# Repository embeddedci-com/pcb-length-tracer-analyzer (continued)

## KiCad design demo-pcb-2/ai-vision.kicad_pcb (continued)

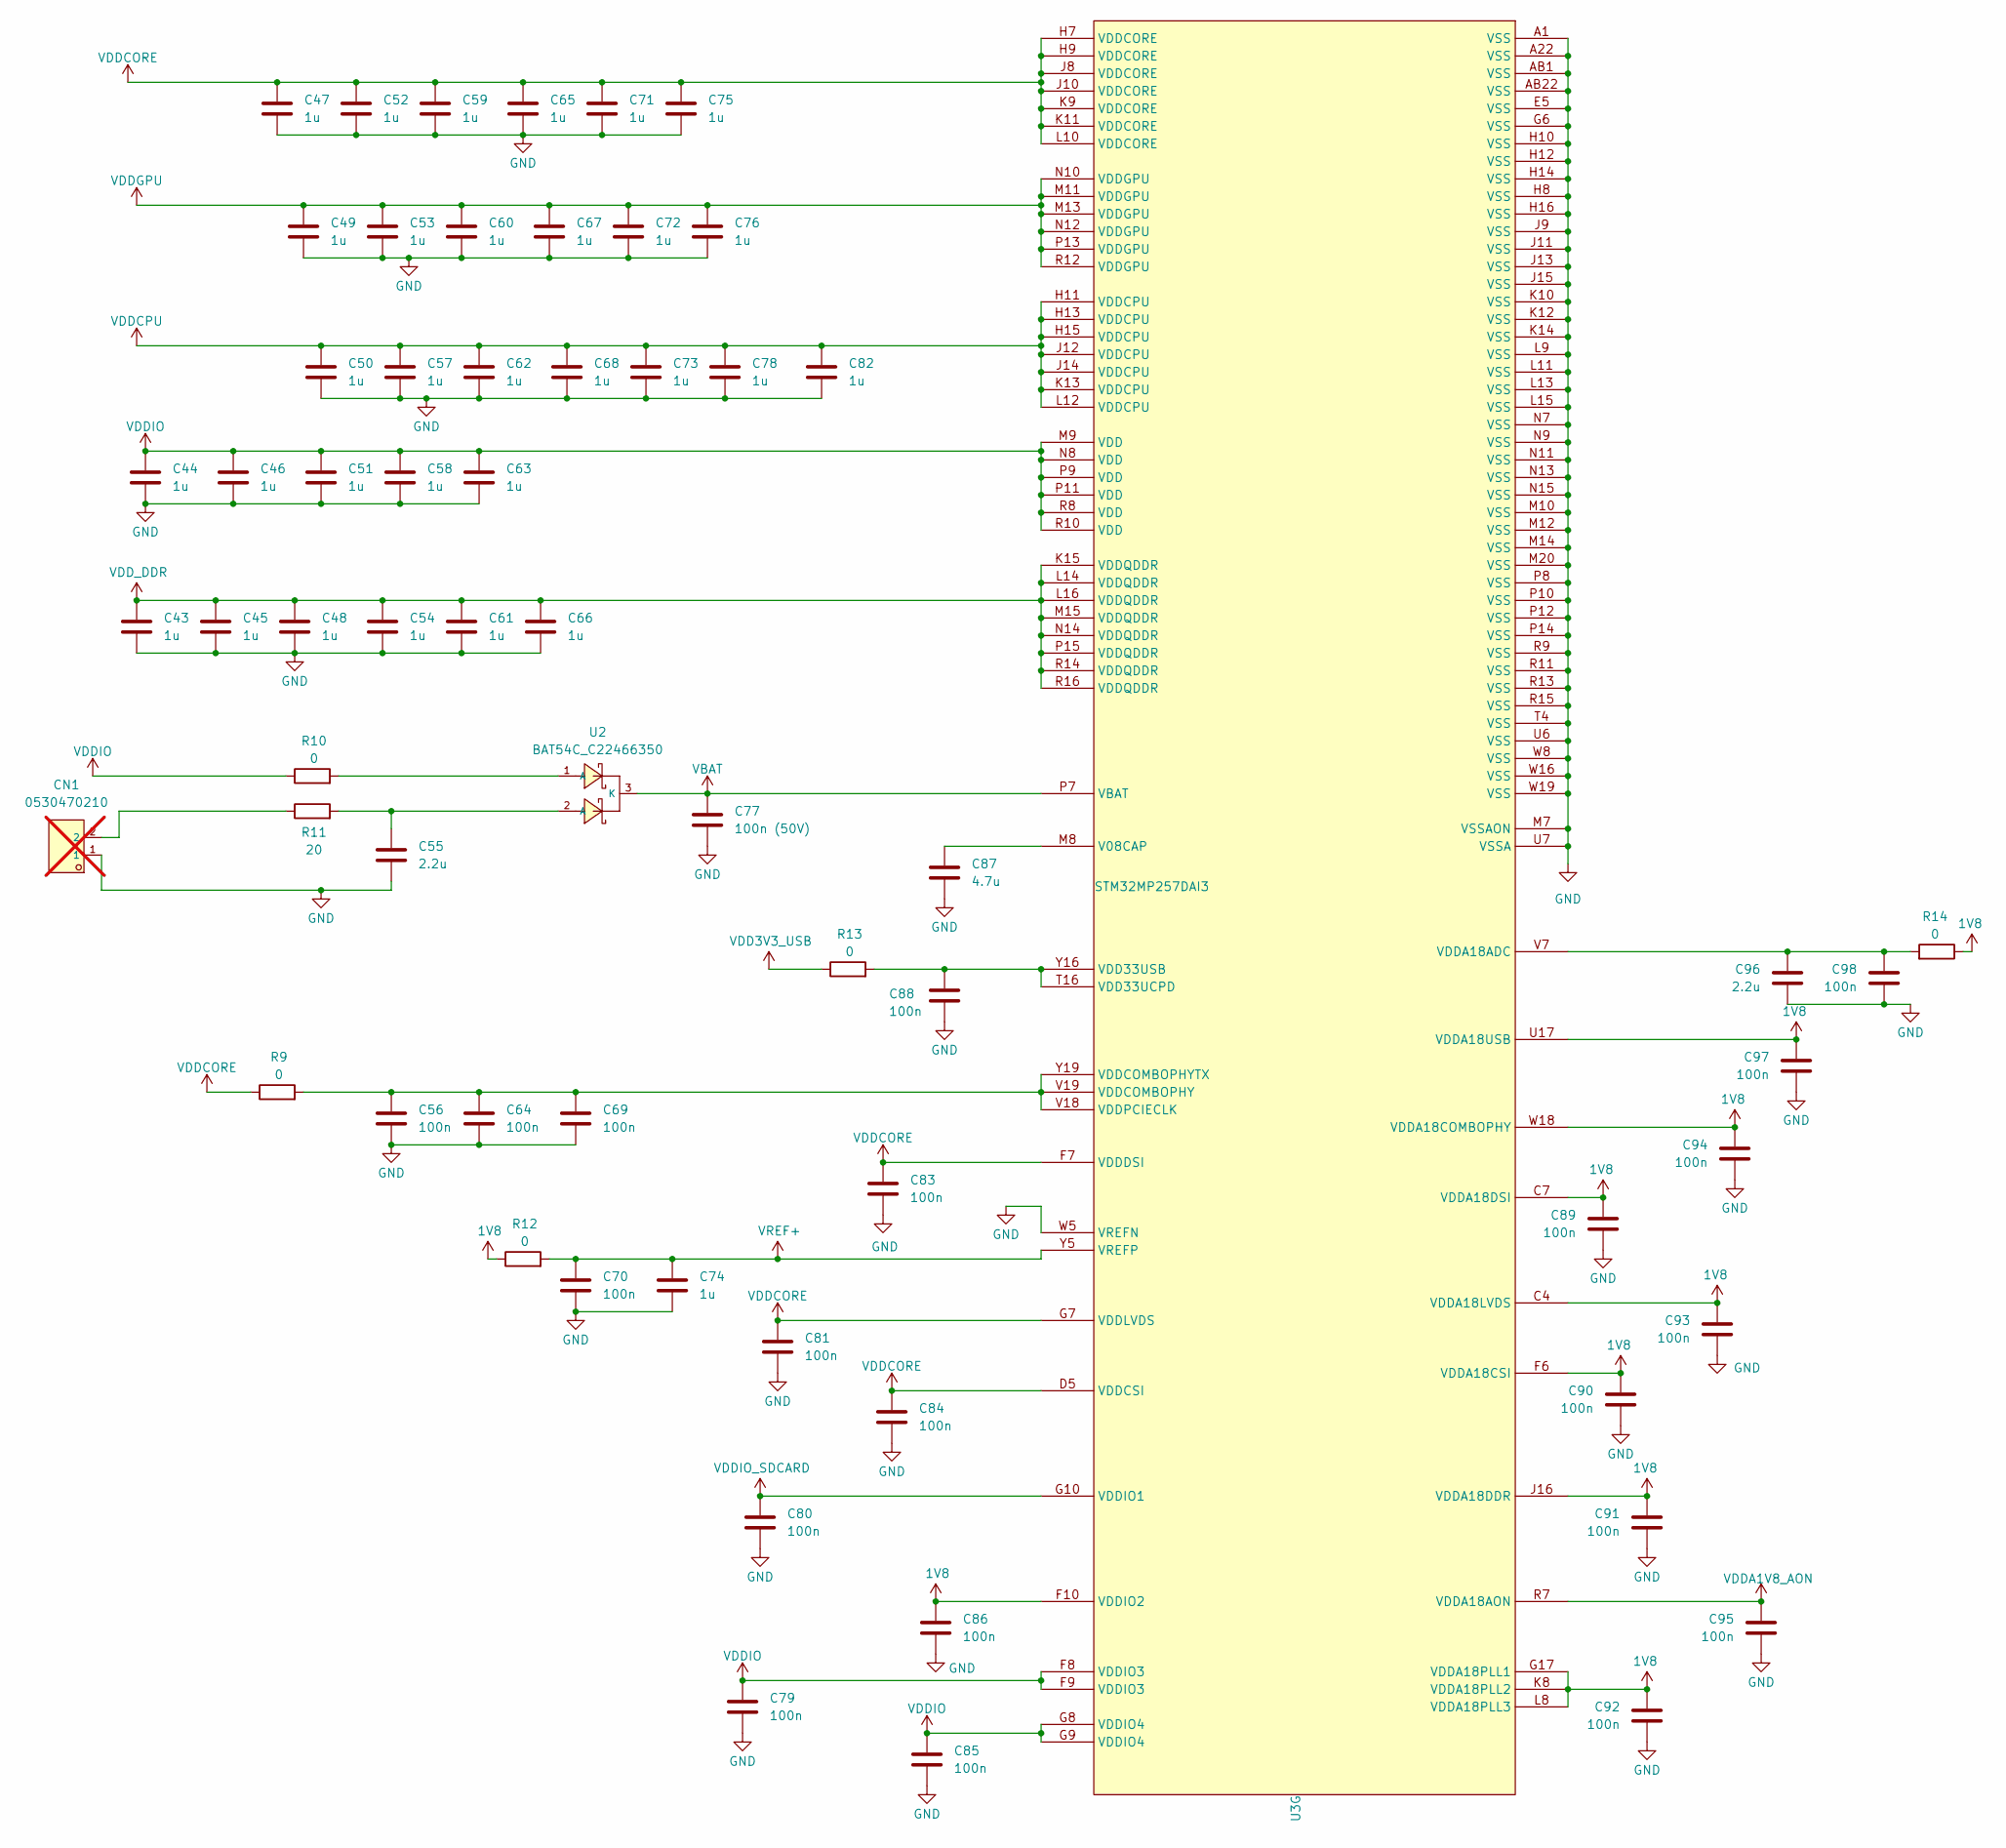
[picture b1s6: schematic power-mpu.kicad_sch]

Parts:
C43, C44, C45, C46, C47, C48, C49, C50, C51, C52, C53, C54, C57, C58, C59, C60, C61, C62, C63, C65, C66, C67, C68, C71, C72, C73, C74, C75, C76, C78, C82: 1u; C_0201_0603Metric; LCSC C76930
C55, C96: 2.2u; C_0805_2012Metric; LCSC C377773
C56, C64, C69, C70, C79, C80, C81, C83, C84, C85, C86, C88, C89, C90, C91, C92, C93, C94, C95, C97, C98: 100n; C_0201_0603Metric; LCSC C76934
C77: 100n (50V); C_0402_1005Metric; LCSC C307331
C87: 4.7u; C_0805_2012Metric; LCSC C1779
CN1: 0530470210; C114130_CONN-TH_0530470210; LCSC C114130; not fitted
R9, R10, R12, R13, R14: 0; R_0402_1005Metric; LCSC C17168
R11: 20; R_0603_1608Metric; LCSC C22950
U2: BAT54C_C22466350; C22466350_SOT-23-3_L2_9-W1_3-P1_90-LS2_8-BR; LCSC C22466350
U3: STM32MP257DAI3; C39969643_TFBGA-436_L18_0-W18_0-0_80-TL_STM32MP257FAI3; PART_TYPE IC; LCSC C39969643

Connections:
1V8: C86.1, C89.1, C90.1, C91.1, C92.1, C93.1, C94.1, C97.1, R12.1, R14.1, U3.C4 (VDDA18LVDS), U3.C7 (VDDA18DSI), U3.F6 (VDDA18CSI), U3.F10 (VDDIO2), U3.G17 (VDDA18PLL1), U3.J16 (VDDA18DDR), U3.K8 (VDDA18PLL2), U3.L8 (VDDA18PLL3), U3.U17 (VDDA18USB), U3.W18 (VDDA18COMBOPHY); also elsewhere on the board
GND: C43.2, C44.2, C45.2, C46.2, C47.2, C48.2, C49.2, C50.2, C51.2, C52.2, C53.2, C54.2, C55.2, C56.2, C57.2, C58.2, C59.2, C60.2, C61.2, C62.2, C63.2, C64.2, C65.2, C66.2, C67.2, C68.2, C69.2, C70.2, C71.2, C72.2, C73.2, C74.2, C75.2, C76.2, C77.2, C78.2, C79.2, C80.2, C81.2, C82.2, C83.2, C84.2, C85.2, C86.2, C87.2, C88.2, C89.2, C90.2, C91.2, C92.2, C93.2, C94.2, C95.2, C96.2, C97.2, C98.2, CN1.1, U3.A1 (VSS), U3.A22 (VSS), U3.AB1 (VSS), U3.AB22 (VSS), U3.E5 (VSS), U3.G6 (VSS), U3.H8 (VSS), U3.H10 (VSS), U3.H12 (VSS), U3.H14 (VSS), U3.H16 (VSS), U3.J9 (VSS), U3.J11 (VSS), U3.J13 (VSS), U3.J15 (VSS), U3.K10 (VSS), U3.K12 (VSS), U3.K14 (VSS), U3.L9 (VSS), U3.L11 (VSS), U3.L13 (VSS), U3.L15 (VSS), U3.M7 (VSSAON), U3.M10 (VSS), U3.M12 (VSS), U3.M14 (VSS), U3.M20 (VSS), U3.N7 (VSS), U3.N9 (VSS), U3.N11 (VSS), U3.N13 (VSS), U3.N15 (VSS), U3.P8 (VSS), U3.P10 (VSS), U3.P12 (VSS), U3.P14 (VSS), U3.R9 (VSS), U3.R11 (VSS), U3.R13 (VSS), U3.R15 (VSS), U3.T4 (VSS), U3.U6 (VSS), U3.U7 (VSSA), U3.W5 (VREFN), U3.W8 (VSS), U3.W16 (VSS), U3.W19 (VSS); also elsewhere on the board
unnamed: C55.1, R11.2, U2.2 (A)
unnamed: CN1.2, R11.1
unnamed: R10.2, U2.1 (A)
unnamed: C87.1, U3.M8 (V08CAP)
unnamed: C88.1, R13.2, U3.T16 (VDD33UCPD), U3.Y16 (VDD33USB)
unnamed: C96.1, C98.1, R14.2, U3.V7 (VDDA18ADC)
unnamed: C56.1, C64.1, C69.1, R9.2, U3.V18 (VDDPCIECLK), U3.V19 (VDDCOMBOPHY), U3.Y19 (VDDCOMBOPHYTX)
VBAT: C77.1, U2.3 (K), U3.P7 (VBAT)
VDD3V3_USB: R13.1; also elsewhere on the board
VDDA1V8_AON: C95.1, U3.R7 (VDDA18AON); also elsewhere on the board
VDDCORE: C47.1, C52.1, C59.1, C65.1, C71.1, C75.1, C81.1, C83.1, C84.1, R9.1, U3.D5 (VDDCSI), U3.F7 (VDDDSI), U3.G7 (VDDLVDS), U3.H7 (VDDCORE), U3.H9 (VDDCORE), U3.J8 (VDDCORE), U3.J10 (VDDCORE), U3.K9 (VDDCORE), U3.K11 (VDDCORE), U3.L10 (VDDCORE); also elsewhere on the board
VDDCPU: C50.1, C57.1, C62.1, C68.1, C73.1, C78.1, C82.1, U3.H11 (VDDCPU), U3.H13 (VDDCPU), U3.H15 (VDDCPU), U3.J12 (VDDCPU), U3.J14 (VDDCPU), U3.K13 (VDDCPU), U3.L12 (VDDCPU); also elsewhere on the board
VDDGPU: C49.1, C53.1, C60.1, C67.1, C72.1, C76.1, U3.M11 (VDDGPU), U3.M13 (VDDGPU), U3.N10 (VDDGPU), U3.N12 (VDDGPU), U3.P13 (VDDGPU), U3.R12 (VDDGPU)
VDDIO: C44.1, C46.1, C51.1, C58.1, C63.1, C79.1, C85.1, R10.1, U3.F8 (VDDIO3), U3.F9 (VDDIO3), U3.G8 (VDDIO4), U3.G9 (VDDIO4), U3.M9 (VDD), U3.N8 (VDD), U3.P9 (VDD), U3.P11 (VDD), U3.R8 (VDD), U3.R10 (VDD); also elsewhere on the board
VDDIO_SDCARD: C80.1, U3.G10 (VDDIO1); also elsewhere on the board
VDD_DDR: C43.1, C45.1, C48.1, C54.1, C61.1, C66.1, U3.K15 (VDDQDDR), U3.L14 (VDDQDDR), U3.L16 (VDDQDDR), U3.M15 (VDDQDDR), U3.N14 (VDDQDDR), U3.P15 (VDDQDDR), U3.R14 (VDDQDDR), U3.R16 (VDDQDDR); also elsewhere on the board
VREF+: C70.1, C74.1, R12.2, U3.Y5 (VREFP)

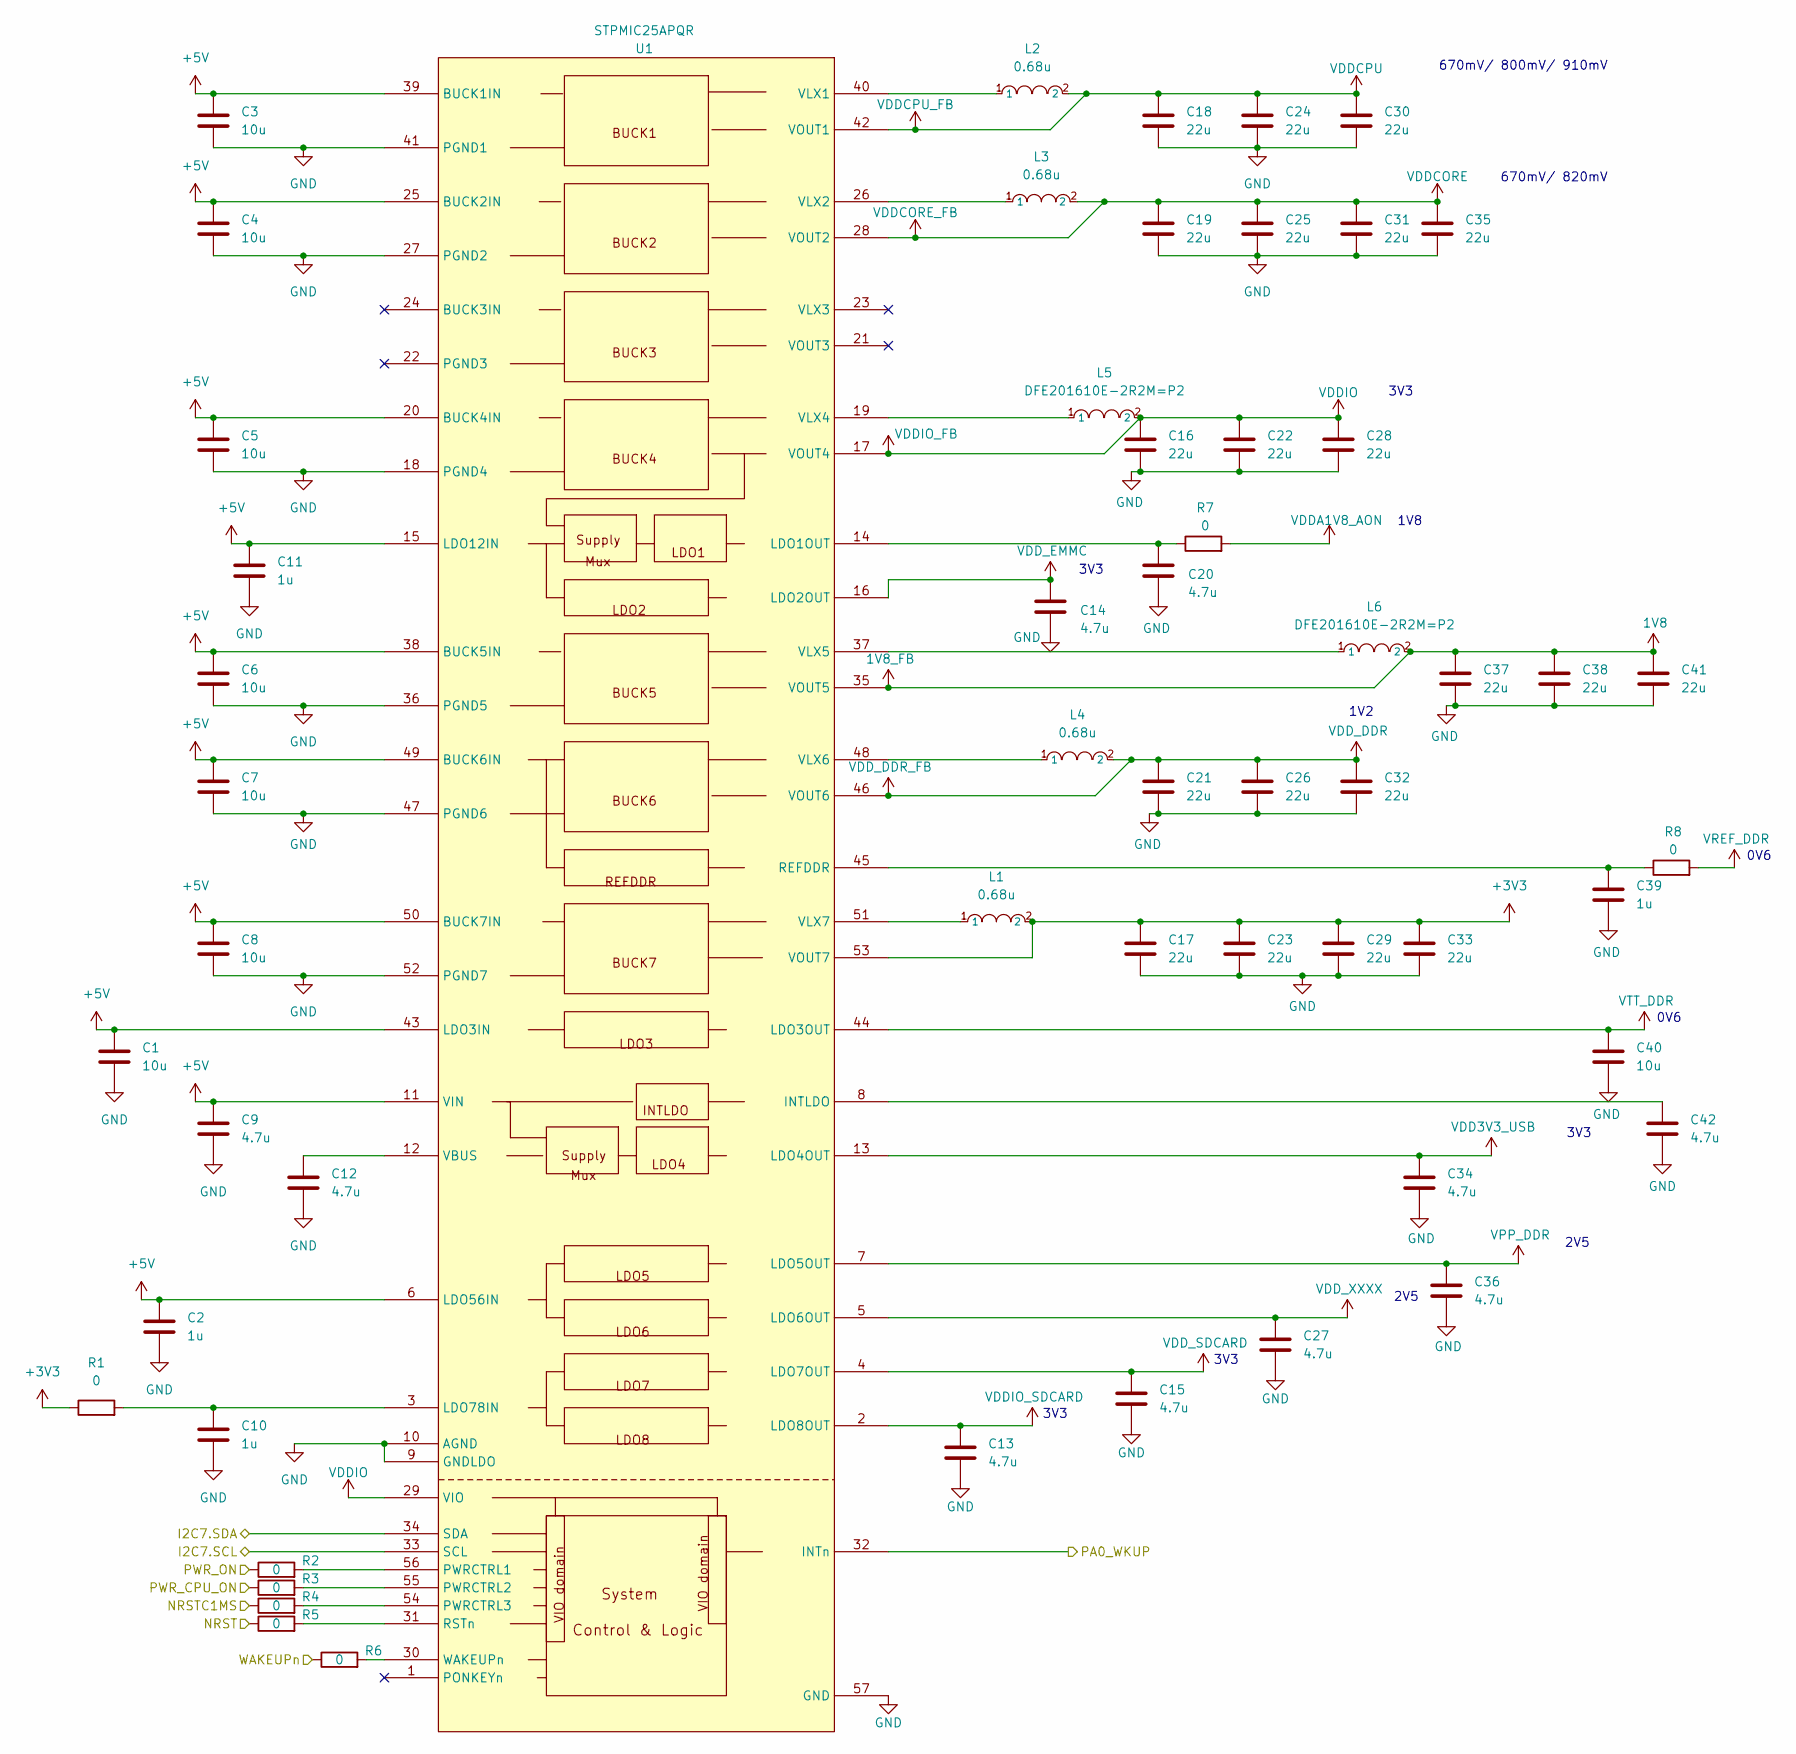
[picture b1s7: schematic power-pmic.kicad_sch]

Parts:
C1, C3, C4, C5, C6, C7, C8, C40: 10u; C_0603_1608Metric; LCSC C96446
C2, C10, C11, C39: 1u; C_0402_1005Metric; LCSC C52923
C9, C12, C13, C14, C15, C20, C27, C34, C36, C42: 4.7u; C_0805_2012Metric; LCSC C1779
C16, C17, C18, C19, C21, C22, C23, C24, C25, C26, C28, C29, C30, C31, C32, C33, C35, C37, C38, C41: 22u; C_0805_2012Metric; LCSC C45783
L1, L3: 0.68u; C2042379_L1008; LCSC C2042379
L2, L4: 0.68u; C237553_L0806; LCSC C237553
L5, L6: DFE201610E-2R2M=P2; C337891_L0806; LCSC C337891
R1, R2, R3, R4, R5, R6, R7, R8: 0; R_0402_1005Metric; LCSC C17168
U1: STPMIC2; C24290186_QFN-56_L6_5-W6_5-P0_40-TL-EP4_5; PART_TYPE IC; LCSC C24290186

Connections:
1V8: C37.1, C38.1, C41.1, L6.2, U1.35 (VOUT5); also elsewhere on the board
+3V3: C17.1, C23.1, C29.1, C33.1, L1.2, R1.1, U1.53 (VOUT7); also elsewhere on the board
+5V: C1.1, C2.1, C3.1, C4.1, C5.1, C6.1, C7.1, C8.1, C9.1, C11.1, U1.6 (LDO56IN), U1.11 (VIN), U1.15 (LDO12IN), U1.20 (BUCK4IN), U1.25 (BUCK2IN), U1.38 (BUCK5IN), U1.39 (BUCK1IN), U1.43 (LDO3IN), U1.49 (BUCK6IN), U1.50 (BUCK7IN); also elsewhere on the board
/MP257/I2C7.SCL: U1.33 (SCL); also elsewhere on the board
/MP257/I2C7.SDA: U1.34 (SDA); also elsewhere on the board
/MP257/PA0_WKUP: U1.32 (INTn); also elsewhere on the board
/MP257/PWR_CPU_ON: R3.1; also elsewhere on the board
/MP257/PWR_ON: R2.1; also elsewhere on the board
/MP257/WAKEUPn: R6.1; also elsewhere on the board
/NRST: R5.1; also elsewhere on the board
/NRSTC1MS: R4.1; also elsewhere on the board
GND: C1.2, C2.2, C3.2, C4.2, C5.2, C6.2, C7.2, C8.2, C9.2, C10.2, C11.2, C12.2, C13.2, C14.2, C15.2, C16.2, C17.2, C18.2, C19.2, C20.2, C21.2, C22.2, C23.2, C24.2, C25.2, C26.2, C27.2, C28.2, C29.2, C30.2, C31.2, C32.2, C33.2, C34.2, C35.2, C36.2, C37.2, C38.2, C39.2, C40.2, C41.2, C42.2, U1.9 (GNDLDO), U1.10 (AGND), U1.18 (PGND4), U1.27 (PGND2), U1.36 (PGND5), U1.41 (PGND1), U1.47 (PGND6), U1.52 (PGND7), U1.57 (GND); also elsewhere on the board
unnamed: C42.1, U1.8 (INTLDO)
unnamed: C20.1, R7.1, U1.14 (LDO1OUT)
unnamed: C10.1, R1.2, U1.3 (LDO78IN)
unnamed: R2.2, U1.56 (PWRCTRL1)
unnamed: R3.2, U1.55 (PWRCTRL2)
unnamed: R4.2, U1.54 (PWRCTRL3)
unnamed: C39.1, R8.1, U1.45 (REFDDR)
unnamed: R5.2, U1.31 (RSTn)
unnamed: C12.1, U1.12 (VBUS)
unnamed: L2.1, U1.40 (VLX1)
unnamed: L3.1, U1.26 (VLX2)
unnamed: L5.1, U1.19 (VLX4)
unnamed: L6.1, U1.37 (VLX5)
unnamed: L4.1, U1.48 (VLX6)
unnamed: L1.1, U1.51 (VLX7)
unnamed: R6.2, U1.30 (WAKEUPn)
VDD3V3_USB: C34.1, U1.13 (LDO4OUT); also elsewhere on the board
VDDA1V8_AON: R7.2; also elsewhere on the board
VDDCORE: C19.1, C25.1, C31.1, C35.1, L3.2, U1.28 (VOUT2); also elsewhere on the board
VDDCPU: C18.1, C24.1, C30.1, L2.2, U1.42 (VOUT1); also elsewhere on the board
VDDIO: C16.1, C22.1, C28.1, L5.2, U1.17 (VOUT4), U1.29 (VIO); also elsewhere on the board
VDDIO_SDCARD: C13.1, U1.2 (LDO8OUT); also elsewhere on the board
VDD_DDR: C21.1, C26.1, C32.1, L4.2, U1.46 (VOUT6); also elsewhere on the board
VDD_EMMC: C14.1, U1.16 (LDO2OUT); also elsewhere on the board
VDD_SDCARD: C15.1, U1.4 (LDO7OUT); also elsewhere on the board
VDD_XXXX: C27.1, U1.5 (LDO6OUT)
VPP_DDR: C36.1, U1.7 (LDO5OUT); also elsewhere on the board
VREF_DDR: R8.2; also elsewhere on the board
VTT_DDR: C40.1, U1.44 (LDO3OUT); also elsewhere on the board

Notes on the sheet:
1V8
3V3
1V2
670mV/ 800mV/ 910mV
2V5
670mV/ 820mV
0V6

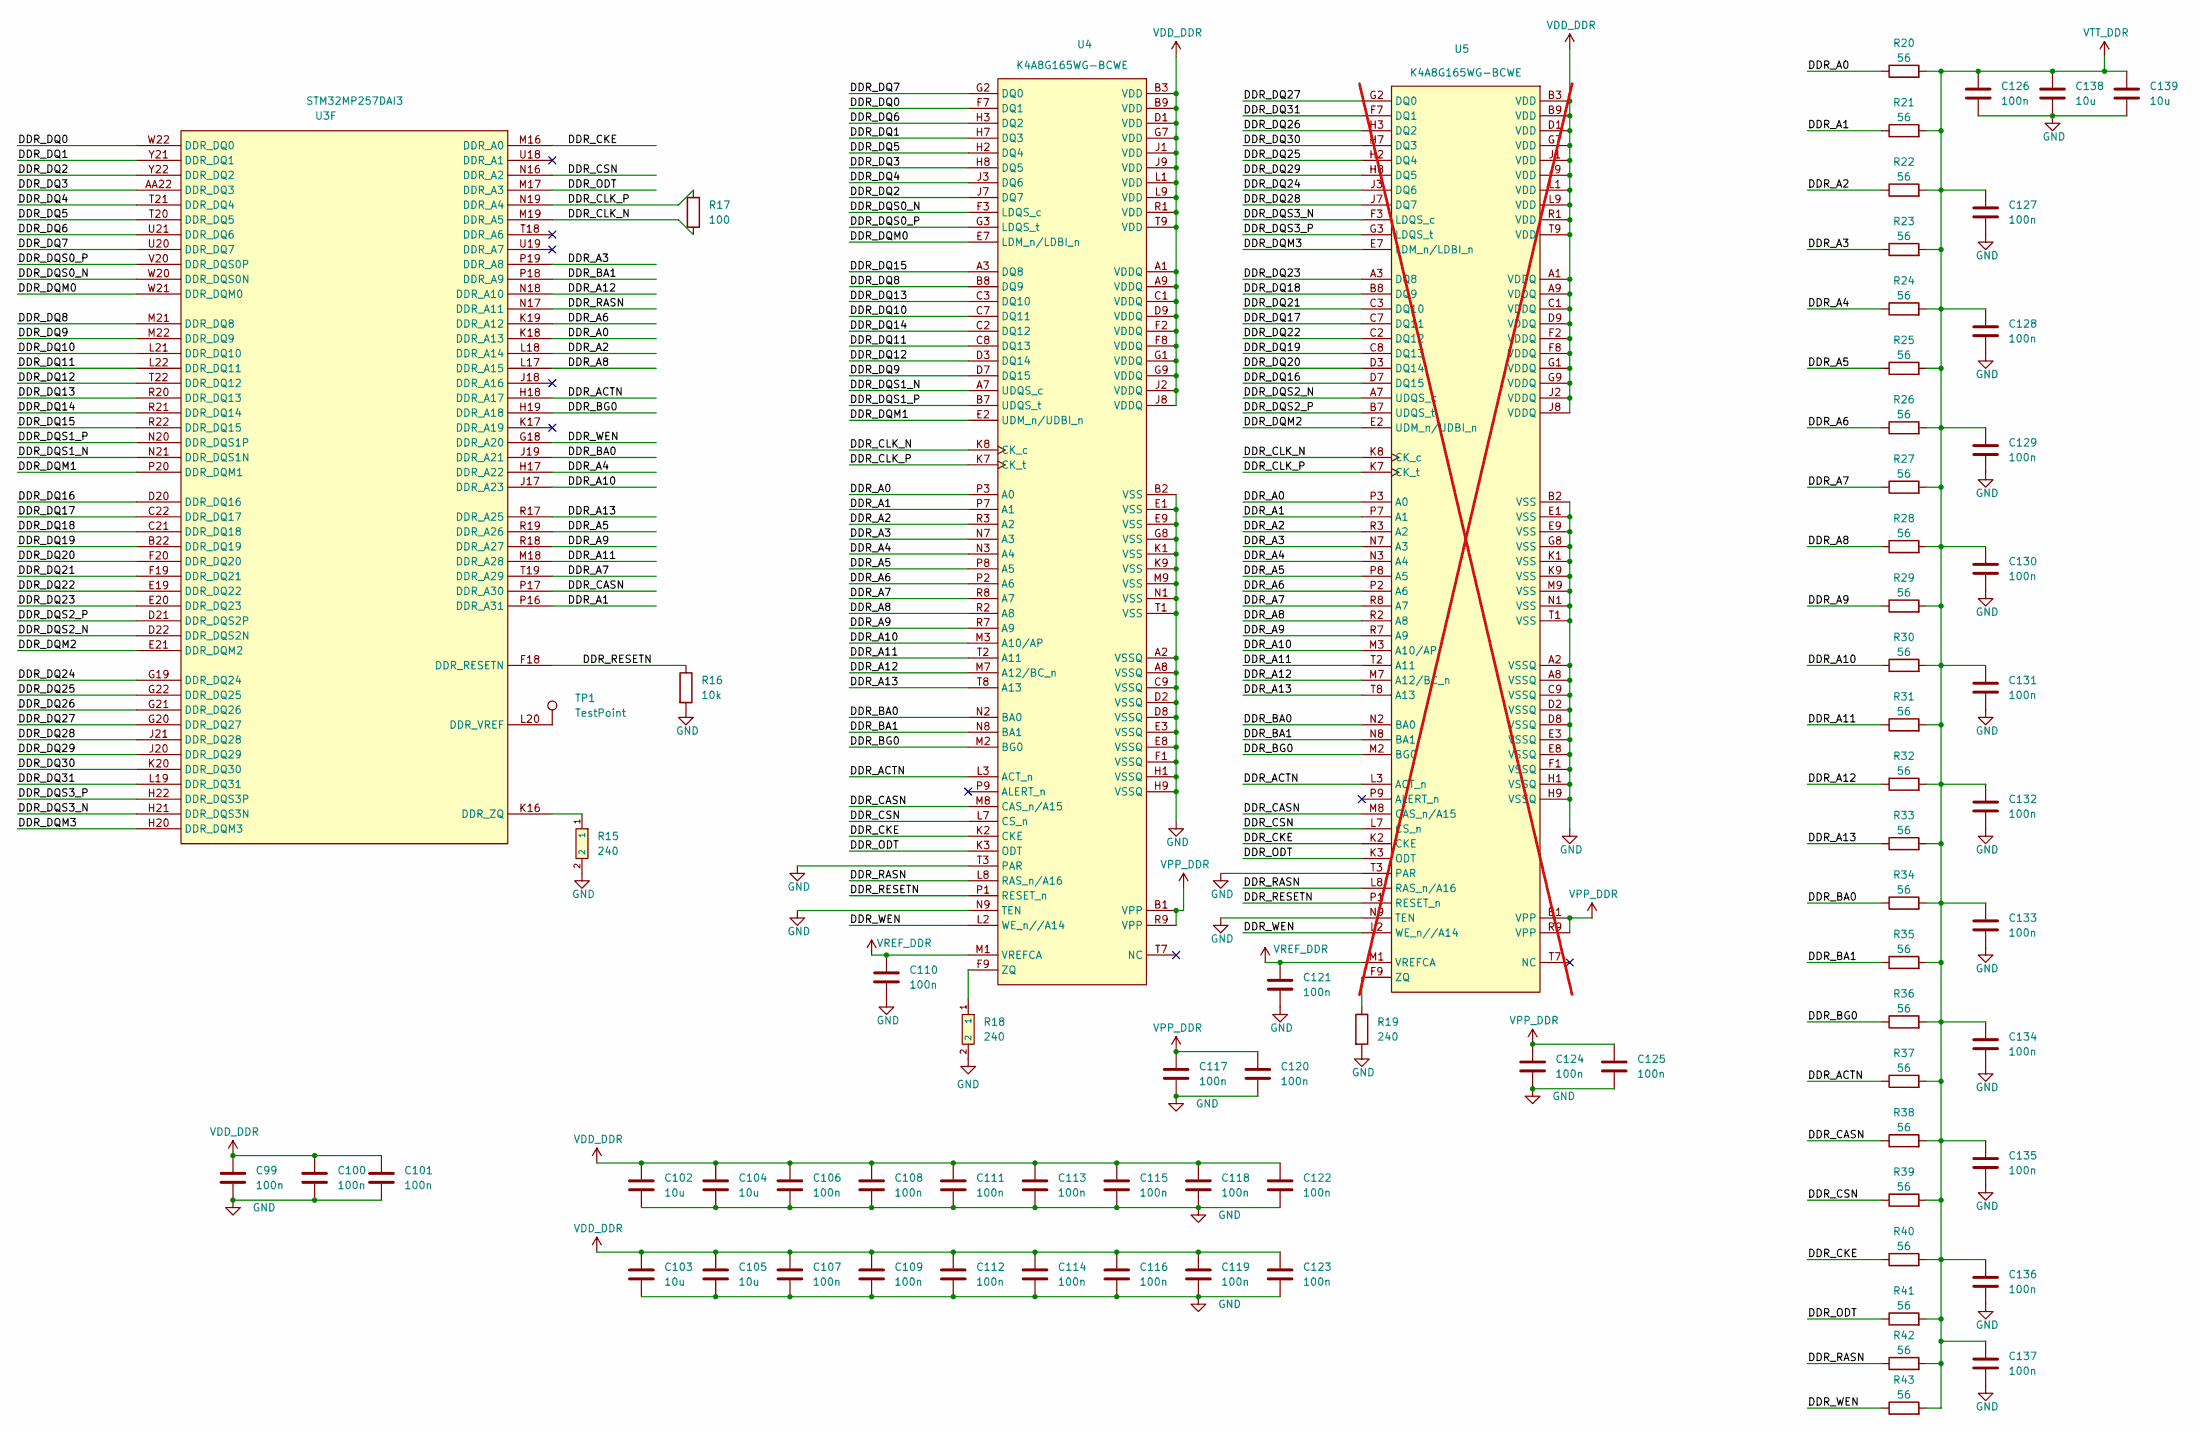
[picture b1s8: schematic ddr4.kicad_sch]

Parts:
C99, C100, C101, C106, C107, C108, C109, C110, C111, C112, C113, C114, C115, C116, C117, C118, C119, C120, C121, C122, C123, C124, C125, C126, C127, C128, C129, C130, C131, C132, C133, C134, C135, C136, C137: 100n; C_0402_1005Metric; LCSC C307331
C102, C103, C104, C105, C138, C139: 10u; C_0603_1608Metric; LCSC C96446
R15, R18: 240; C155745_R0201; LCSC C155745
R16: 10k; R_0402_1005Metric; LCSC C25744
R17: 100; R_0402_1005Metric; LCSC C25076
R19: 240; R_0603_1608Metric; LCSC C23350
R20, R21, R22, R23, R24, R25, R26, R27, R28, R29, R30, R31, R32, R33, R34, R35, R36, R37, R38, R39, R40, R41, R42, R43: 56; R_0402_1005Metric; LCSC C25127
TP1: TestPoint; TestPoint_Pad_1.0x1.0mm
U3: STM32MP257DAI3; C39969643_TFBGA-436_L18_0-W18_0-0_80-TL_STM32MP257FAI3; PART_TYPE IC; LCSC C39969643
U4: K4A8G165WG-BCWE; C41368581_FBGA-96_L13_3-W7_5-R16-C6-P0_80-TL; LCSC C41368581
U5: K4A8G165WG-BCWE; C41368581_FBGA-96_L13_3-W7_5-R16-C6-P0_80-TL; LCSC C41368581; not fitted

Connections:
/ddr4/DDR_A0: R20.1, U3.K18 (DDR_A13), U4.P3 (A0), U5.P3 (A0)
/ddr4/DDR_A1: R21.1, U3.P16 (DDR_A31), U4.P7 (A1), U5.P7 (A1)
/ddr4/DDR_A2: R22.1, U3.L18 (DDR_A14), U4.R3 (A2), U5.R3 (A2)
/ddr4/DDR_A3: R23.1, U3.P19 (DDR_A8), U4.N7 (A3), U5.N7 (A3)
/ddr4/DDR_A4: R24.1, U3.H17 (DDR_A22), U4.N3 (A4), U5.N3 (A4)
/ddr4/DDR_A5: R25.1, U3.R19 (DDR_A26), U4.P8 (A5), U5.P8 (A5)
/ddr4/DDR_A6: R26.1, U3.K19 (DDR_A12), U4.P2 (A6), U5.P2 (A6)
/ddr4/DDR_A7: R27.1, U3.T19 (DDR_A29), U4.R8 (A7), U5.R8 (A7)
/ddr4/DDR_A8: R28.1, U3.L17 (DDR_A15), U4.R2 (A8), U5.R2 (A8)
/ddr4/DDR_A9: R29.1, U3.R18 (DDR_A27), U4.R7 (A9), U5.R7 (A9)
/ddr4/DDR_A10: R30.1, U3.J17 (DDR_A23), U4.M3 (A10/AP), U5.M3 (A10/AP)
/ddr4/DDR_A11: R31.1, U3.M18 (DDR_A28), U4.T2 (A11), U5.T2 (A11)
/ddr4/DDR_A12: R32.1, U3.N18 (DDR_A10), U4.M7 (A12/BC_n), U5.M7 (A12/BC_n)
/ddr4/DDR_A13: R33.1, U3.R17 (DDR_A25), U4.T8 (A13), U5.T8 (A13)
/ddr4/DDR_ACTN: R37.1, U3.H18 (DDR_A17), U4.L3 (ACT_n), U5.L3 (ACT_n)
/ddr4/DDR_BA0: R34.1, U3.J19 (DDR_A21), U4.N2 (BA0), U5.N2 (BA0)
/ddr4/DDR_BA1: R35.1, U3.P18 (DDR_A9), U4.N8 (BA1), U5.N8 (BA1)
/ddr4/DDR_BG0: R36.1, U3.H19 (DDR_A18), U4.M2 (BG0), U5.M2 (BG0)
/ddr4/DDR_CASN: R38.1, U3.P17 (DDR_A30), U4.M8 (CAS_n/A15), U5.M8 (CAS_n/A15)
/ddr4/DDR_CKE: R40.1, U3.M16 (DDR_A0), U4.K2 (CKE), U5.K2 (CKE)
/ddr4/DDR_CLK_N: R17.2, U3.M19 (DDR_A5), U4.K8 (CK_c), U5.K8 (CK_c)
/ddr4/DDR_CLK_P: R17.1, U3.N19 (DDR_A4), U4.K7 (CK_t), U5.K7 (CK_t)
/ddr4/DDR_CSN: R39.1, U3.N16 (DDR_A2), U4.L7 (CS_n), U5.L7 (CS_n)
/ddr4/DDR_DQ0: U3.W22 (DDR_DQ0), U4.F7 (DQ1)
/ddr4/DDR_DQ1: U3.Y21 (DDR_DQ1), U4.H7 (DQ3)
/ddr4/DDR_DQ2: U3.Y22 (DDR_DQ2), U4.J7 (DQ7)
/ddr4/DDR_DQ3: U3.AA22 (DDR_DQ3), U4.H8 (DQ5)
/ddr4/DDR_DQ4: U3.T21 (DDR_DQ4), U4.J3 (DQ6)
/ddr4/DDR_DQ5: U3.T20 (DDR_DQ5), U4.H2 (DQ4)
/ddr4/DDR_DQ6: U3.U21 (DDR_DQ6), U4.H3 (DQ2)
/ddr4/DDR_DQ7: U3.U20 (DDR_DQ7), U4.G2 (DQ0)
/ddr4/DDR_DQ8: U3.M21 (DDR_DQ8), U4.B8 (DQ9)
/ddr4/DDR_DQ9: U3.M22 (DDR_DQ9), U4.D7 (DQ15)
/ddr4/DDR_DQ10: U3.L21 (DDR_DQ10), U4.C7 (DQ11)
/ddr4/DDR_DQ11: U3.L22 (DDR_DQ11), U4.C8 (DQ13)
/ddr4/DDR_DQ12: U3.T22 (DDR_DQ12), U4.D3 (DQ14)
/ddr4/DDR_DQ13: U3.R20 (DDR_DQ13), U4.C3 (DQ10)
/ddr4/DDR_DQ14: U3.R21 (DDR_DQ14), U4.C2 (DQ12)
/ddr4/DDR_DQ15: U3.R22 (DDR_DQ15), U4.A3 (DQ8)
/ddr4/DDR_DQ16: U3.D20 (DDR_DQ16), U5.D7 (DQ15)
/ddr4/DDR_DQ17: U3.C22 (DDR_DQ17), U5.C7 (DQ11)
/ddr4/DDR_DQ18: U3.C21 (DDR_DQ18), U5.B8 (DQ9)
/ddr4/DDR_DQ19: U3.B22 (DDR_DQ19), U5.C8 (DQ13)
/ddr4/DDR_DQ20: U3.F20 (DDR_DQ20), U5.D3 (DQ14)
/ddr4/DDR_DQ21: U3.F19 (DDR_DQ21), U5.C3 (DQ10)
/ddr4/DDR_DQ22: U3.E19 (DDR_DQ22), U5.C2 (DQ12)
/ddr4/DDR_DQ23: U3.E20 (DDR_DQ23), U5.A3 (DQ8)
/ddr4/DDR_DQ24: U3.G19 (DDR_DQ24), U5.J3 (DQ6)
/ddr4/DDR_DQ25: U3.G22 (DDR_DQ25), U5.H2 (DQ4)
/ddr4/DDR_DQ26: U3.G21 (DDR_DQ26), U5.H3 (DQ2)
/ddr4/DDR_DQ27: U3.G20 (DDR_DQ27), U5.G2 (DQ0)
/ddr4/DDR_DQ28: U3.J21 (DDR_DQ28), U5.J7 (DQ7)
/ddr4/DDR_DQ29: U3.J20 (DDR_DQ29), U5.H8 (DQ5)
/ddr4/DDR_DQ30: U3.K20 (DDR_DQ30), U5.H7 (DQ3)
/ddr4/DDR_DQ31: U3.L19 (DDR_DQ31), U5.F7 (DQ1)
/ddr4/DDR_DQM0: U3.W21 (DDR_DQM0), U4.E7 (LDM_n/LDBI_n)
/ddr4/DDR_DQM1: U3.P20 (DDR_DQM1), U4.E2 (UDM_n/UDBI_n)
/ddr4/DDR_DQM2: U3.E21 (DDR_DQM2), U5.E2 (UDM_n/UDBI_n)
/ddr4/DDR_DQM3: U3.H20 (DDR_DQM3), U5.E7 (LDM_n/LDBI_n)
/ddr4/DDR_DQS0_N: U3.W20 (DDR_DQS0N), U4.F3 (LDQS_c)
/ddr4/DDR_DQS0_P: U3.V20 (DDR_DQS0P), U4.G3 (LDQS_t)
/ddr4/DDR_DQS1_N: U3.N21 (DDR_DQS1N), U4.A7 (UDQS_c)
/ddr4/DDR_DQS1_P: U3.N20 (DDR_DQS1P), U4.B7 (UDQS_t)
/ddr4/DDR_DQS2_N: U3.D22 (DDR_DQS2N), U5.A7 (UDQS_c)
/ddr4/DDR_DQS2_P: U3.D21 (DDR_DQS2P), U5.B7 (UDQS_t)
/ddr4/DDR_DQS3_N: U3.H21 (DDR_DQS3N), U5.F3 (LDQS_c)
/ddr4/DDR_DQS3_P: U3.H22 (DDR_DQS3P), U5.G3 (LDQS_t)
/ddr4/DDR_ODT: R41.1, U3.M17 (DDR_A3), U4.K3 (ODT), U5.K3 (ODT)
/ddr4/DDR_RASN: R42.1, U3.N17 (DDR_A11), U4.L8 (RAS_n/A16), U5.L8 (RAS_n/A16)
/ddr4/DDR_RESETN: R16.1, U3.F18 (DDR_RESETN), U4.P1 (RESET_n), U5.P1 (RESET_n)
/ddr4/DDR_WEN: R43.1, U3.G18 (DDR_A20), U4.L2 (WE_n//A14), U5.L2 (WE_n//A14)
GND: C99.2, C100.2, C101.2, C102.2, C103.2, C104.2, C105.2, C106.2, C107.2, C108.2, C109.2, C110.2, C111.2, C112.2, C113.2, C114.2, C115.2, C116.2, C117.2, C118.2, C119.2, C120.2, C121.2, C122.2, C123.2, C124.2, C125.2, C126.2, C127.2, C128.2, C129.2, C130.2, C131.2, C132.2, C133.2, C134.2, C135.2, C136.2, C137.2, C138.2, C139.2, R15.2, R16.2, R18.2, R19.2, U4.A2 (VSSQ), U4.A8 (VSSQ), U4.B2 (VSS), U4.C9 (VSSQ), U4.D2 (VSSQ), U4.D8 (VSSQ), U4.E1 (VSS), U4.E3 (VSSQ), U4.E8 (VSSQ), U4.E9 (VSS), U4.F1 (VSSQ), U4.G8 (VSS), U4.H1 (VSSQ), U4.H9 (VSSQ), U4.K1 (VSS), U4.K9 (VSS), U4.M9 (VSS), U4.N1 (VSS), U4.N9 (TEN), U4.T1 (VSS), U4.T3 (PAR), U5.A2 (VSSQ), U5.A8 (VSSQ), U5.B2 (VSS), U5.C9 (VSSQ), U5.D2 (VSSQ), U5.D8 (VSSQ), U5.E1 (VSS), U5.E3 (VSSQ), U5.E8 (VSSQ), U5.E9 (VSS), U5.F1 (VSSQ), U5.G8 (VSS), U5.H1 (VSSQ), U5.H9 (VSSQ), U5.K1 (VSS), U5.K9 (VSS), U5.M9 (VSS), U5.N1 (VSS), U5.N9 (TEN), U5.T1 (VSS), U5.T3 (PAR); also elsewhere on the board
unnamed: TP1.1 (1_1), U3.L20 (DDR_VREF)
unnamed: R15.1, U3.K16 (DDR_ZQ)
unnamed: R18.1, U4.F9 (ZQ)
unnamed: R19.1, U5.F9 (ZQ)
VDD_DDR: C99.1, C100.1, C101.1, C102.1, C103.1, C104.1, C105.1, C106.1, C107.1, C108.1, C109.1, C111.1, C112.1, C113.1, C114.1, C115.1, C116.1, C118.1, C119.1, C122.1, C123.1, U4.A1 (VDDQ), U4.A9 (VDDQ), U4.B3 (VDD), U4.B9 (VDD), U4.C1 (VDDQ), U4.D1 (VDD), U4.D9 (VDDQ), U4.F2 (VDDQ), U4.F8 (VDDQ), U4.G1 (VDDQ), U4.G7 (VDD), U4.G9 (VDDQ), U4.J1 (VDD), U4.J2 (VDDQ), U4.J8 (VDDQ), U4.J9 (VDD), U4.L1 (VDD), U4.L9 (VDD), U4.R1 (VDD), U4.T9 (VDD), U5.A1 (VDDQ), U5.A9 (VDDQ), U5.B3 (VDD), U5.B9 (VDD), U5.C1 (VDDQ), U5.D1 (VDD), U5.D9 (VDDQ), U5.F2 (VDDQ), U5.F8 (VDDQ), U5.G1 (VDDQ), U5.G7 (VDD), U5.G9 (VDDQ), U5.J1 (VDD), U5.J2 (VDDQ), U5.J8 (VDDQ), U5.J9 (VDD), U5.L1 (VDD), U5.L9 (VDD), U5.R1 (VDD), U5.T9 (VDD); also elsewhere on the board
VPP_DDR: C117.1, C120.1, C124.1, C125.1, U4.B1 (VPP), U4.R9 (VPP), U5.B1 (VPP), U5.R9 (VPP); also elsewhere on the board
VREF_DDR: C110.1, C121.1, U4.M1 (VREFCA), U5.M1 (VREFCA); also elsewhere on the board
VTT_DDR: C126.1, C127.1, C128.1, C129.1, C130.1, C131.1, C132.1, C133.1, C134.1, C135.1, C136.1, C137.1, C138.1, C139.1, R20.2, R21.2, R22.2, R23.2, R24.2, R25.2, R26.2, R27.2, R28.2, R29.2, R30.2, R31.2, R32.2, R33.2, R34.2, R35.2, R36.2, R37.2, R38.2, R39.2, R40.2, R41.2, R42.2, R43.2; also elsewhere on the board

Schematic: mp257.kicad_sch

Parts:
C140: 10n; C_0402_1005Metric; LCSC C15195
C141, C142, C144: 100n; C_0402_1005Metric; LCSC C307331
C143, C145: 20pf; C_0402_1005Metric; LCSC C1554
R44, R45, R47, R49: 1k; R_0402_1005Metric; LCSC C11702
R46, R48, R51, R53: 1.5k; R_0402_1005Metric; LCSC C25867
R50, R52: 10k; R_0402_1005Metric; LCSC C25744
R54: 22; R_0402_1005Metric; LCSC C25092
R55: 0; R_0402_1005Metric; LCSC C17168
SW1: TS-1088-AR02016; C720477_SW-SMD_L3_9-W3_0-P4_45; LCSC C720477
U3: STM32MP257DAI3; C39969643_TFBGA-436_L18_0-W18_0-0_80-TL_STM32MP257FAI3; PART_TYPE IC; LCSC C39969643
U6: DSHP04TSGER; C3293144_SW-SMD_8P-L6_7-W5_4-P1_27-LS8_4; LCSC C3293144
U7: PZ2.54-2*20; C5224014_HDR-TH_40P-P2_54-V-M-R2-C20-S2_54; LCSC C5224014
X1: 32.768KHz ±20ppm 12.5pF; C32346_FC-135R_L3_2-W1_5; LCSC C32346
X2: YC40MUBCE2O; C54307909_OSC-SMD_4P-L3_2-W2_5-BL_5; LCSC C54307909

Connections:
+3V3: C141.1, U7.1, U7.17; also elsewhere on the board
+5V: C144.1, U7.2, U7.4; also elsewhere on the board
/MIPI/CAM_ENABLE: U3.G5 (PI0); also elsewhere on the board
/MIPI/CAM_RESET: U3.L6 (PI7); also elsewhere on the board
/MIPI/I2C2.SCL: R48.2, U3.B11 (PB5), U7.26; also elsewhere on the board
/MIPI/I2C2.SDA: R46.2, U3.D10 (PB4), U7.27; also elsewhere on the board
/MIPI/IMU_INT1: U3.J6 (PI3); also elsewhere on the board
/MIPI/IMU_INT2: U3.K6 (PI4); also elsewhere on the board
/MIPI/TOF_INT: U3.J5 (PI2); also elsewhere on the board
/MIPI/TOF_LPn: U3.K4 (PG7); also elsewhere on the board
/MP257/ETH1.CLK125: U3.AB12 (PH9); also elsewhere on the board
/MP257/ETH1.NRST: U3.M1 (PJ9); also elsewhere on the board
/MP257/GPIO.GPIO7: U3.Y3 (PJ1), U7.24
/MP257/GPIO.SAI2_FSA: U3.AA3 (PJ3), U7.35
/MP257/GPIO.SAI2_SCKA: U3.M5 (PJ11), U7.12
/MP257/GPIO.SAI2_SDA: U3.L2 (PJ12), U7.32
/MP257/GPIO.SAI2_SDB: U3.AB3 (PJ2), U7.34
/MP257/GPIO.SDMMC3_CK: R54.1, U3.D19 (PB13)
/MP257/GPIO.SDMMC3_CMD: U3.A21 (PD12), U7.10
/MP257/GPIO.SDMMC3_D0: U3.C20 (PB14), U7.18
/MP257/GPIO.SDMMC3_D1: U3.B21 (PD13), U7.20
/MP257/GPIO.SDMMC3_D2: U3.B20 (PB12), U7.37
/MP257/GPIO.SDMMC3_D3: U3.E18 (PI11), U7.13
/MP257/GPIO.SPI3_MISO: U3.A11 (PB10), U7.21
/MP257/GPIO.SPI3_MOSI: U3.G11 (PB8), U7.19
/MP257/GPIO.SPI3_NSS: U3.D11 (PB1), U7.22
/MP257/GPIO.SPI3_SCK: U3.D12 (PB7), U7.23
/MP257/GPIO.TIM8_CH1: U3.V4 (PJ5), U7.33
/MP257/GPIO.TIM8_CH4: U3.W3 (PJ4), U7.29
/MP257/GPIO.TIM10_CH1: U3.A12 (PB9), U7.28
/MP257/GPIO.TIM12_CH2: U3.B12 (PB11), U7.31
/MP257/GPIO.USART6_CTS: U3.L7 (PF15), U7.30
/MP257/GPIO.USART6_RTS: U3.L1 (PG5), U7.11
/MP257/GPIO.USART6_RX: U3.H1 (PF14), U7.16
/MP257/GPIO.USART6_TX: U3.L4 (PF13), U7.14
/MP257/I2C7.SCL: R51.2, U3.F16 (PD15); also elsewhere on the board
/MP257/I2C7.SDA: R53.2, U3.G15 (PD14); also elsewhere on the board
/MP257/I2C8.SCL: U3.R5 (PZ4), U7.5
/MP257/I2C8.SDA: U3.N4 (PZ3), U7.3
/MP257/MCO1: U3.Y6 (PF11), U7.7
/MP257/OSC32_IN: C143.1, U3.R1 (OSC32_IN), X1.2
/MP257/OSC32_OUT: R55.1, U3.R2 (OSC32_OUT)
/MP257/OSC_IN: U3.V3 (OSC_IN), X2.3 (OUT)
/MP257/PA0_WKUP: U3.Y2 (PA0); also elsewhere on the board
/MP257/PWR_CPU_ON: R52.1, U3.T6 (PWR_CPUON); also elsewhere on the board
/MP257/PWR_ON: U3.T5 (PWR_ON); also elsewhere on the board
/MP257/SDMMC1_CK: U3.D16 (PE3); also elsewhere on the board
/MP257/SDMMC1_CMD: U3.C16 (PE2); also elsewhere on the board
/MP257/SDMMC1_D0: U3.B17 (PE4); also elsewhere on the board
/MP257/SDMMC1_D1: U3.C17 (PE5); also elsewhere on the board
/MP257/SDMMC1_D2: U3.A16 (PE0); also elsewhere on the board
/MP257/SDMMC1_D3: U3.B16 (PE1); also elsewhere on the board
/MP257/SWCLK: U3.AA1 (JTCK_SWCLK), U7.38
/MP257/SWDIO: U3.Y1 (JTMS_SWDIO), U7.36
/MP257/SWO: U3.W1 (JTDO_TRACESWO), U7.40
/MP257/WAKEUPn: U3.P6 (PC13); also elsewhere on the board
/MP257/emmc_clk: U3.A20 (PE14); also elsewhere on the board
/MP257/emmc_cmd: U3.F17 (PE15); also elsewhere on the board
/MP257/emmc_d0: U3.B19 (PE13); also elsewhere on the board
/MP257/emmc_d1: U3.E17 (PE11); also elsewhere on the board
/MP257/emmc_d2: U3.C18 (PE8); also elsewhere on the board
/MP257/emmc_d3: U3.C19 (PE12); also elsewhere on the board
/MP257/emmc_d4: U3.A19 (PE10); also elsewhere on the board
/MP257/emmc_d5: U3.D18 (PE9); also elsewhere on the board
/MP257/emmc_d6: U3.E16 (PE6); also elsewhere on the board
/MP257/emmc_d7: U3.D17 (PE7); also elsewhere on the board
/MP257/flash_clk: U3.D14 (PD0); also elsewhere on the board
/MP257/flash_cs: U3.C15 (PD3); also elsewhere on the board
/MP257/flash_io0: U3.C14 (PD4); also elsewhere on the board
/MP257/flash_io1: U3.B15 (PD5); also elsewhere on the board
/MP257/flash_io2: U3.A15 (PD6); also elsewhere on the board
/MP257/flash_io3: U3.D15 (PD7); also elsewhere on the board
/MP257/uSD_DETECT: U3.B13 (PD9); also elsewhere on the board
/NRST: C140.1, SW1.1, U3.U3 (NRST); also elsewhere on the board
/NRSTC1MS: R50.2, R52.2, U3.T3 (NRSTC1MS); also elsewhere on the board
/ethernet/ETH1.CLK: U3.W10 (PF3); also elsewhere on the board
/ethernet/ETH1.GTX_CLK: U3.AA12 (PC0); also elsewhere on the board
/ethernet/ETH1.MDC: U3.V12 (PF0); also elsewhere on the board
/ethernet/ETH1.MDINT: U3.U12 (PA12); also elsewhere on the board
/ethernet/ETH1.MDIO: U3.V10 (PF2); also elsewhere on the board
/ethernet/ETH1.RXD0: U3.W11 (PF1); also elsewhere on the board
/ethernet/ETH1.RXD1: U3.Y11 (PC2); also elsewhere on the board
/ethernet/ETH1.RXD2: U3.AA11 (PH12); also elsewhere on the board
/ethernet/ETH1.RXD3: U3.AB11 (PH13); also elsewhere on the board
/ethernet/ETH1.RX_CLK: U3.U10 (PA14); also elsewhere on the board
/ethernet/ETH1.RX_CTL: U3.W12 (PA11); also elsewhere on the board
/ethernet/ETH1.TXD0: U3.T10 (PA15); also elsewhere on the board
/ethernet/ETH1.TXD1: U3.V11 (PC1); also elsewhere on the board
/ethernet/ETH1.TXD2: U3.U11 (PH10); also elsewhere on the board
/ethernet/ETH1.TXD3: U3.T11 (PH11); also elsewhere on the board
/ethernet/ETH1.TX_CTL: U3.Y12 (PA13); also elsewhere on the board
/expansion/PCIE.CLKREQN: U3.U15 (PJ0); also elsewhere on the board
/expansion/PCIE.NWAKE: U3.AA15 (PH5); also elsewhere on the board
/expansion/PCIE.RSTN: U3.M2 (PJ8); also elsewhere on the board
GND: C140.2, C141.2, C142.2, C143.2, C144.2, C145.2, SW1.2, U7.6, U7.8, U7.9, U7.25, U7.39, X2.2 (GND); also elsewhere on the board
unnamed: C145.1, R55.2, X1.1
unnamed: R44.2, U6.5
unnamed: R45.2, U6.6
unnamed: R47.2, U6.7
unnamed: R49.2, U6.8
unnamed: R54.2, U7.15
unnamed: U3.R4 (BOOT0), U6.1
unnamed: U3.R3 (BOOT1), U6.2
unnamed: U3.T2 (BOOT2), U6.3
unnamed: U3.T1 (BOOT3), U6.4
VDDA1V8_AON: C142.1, U3.T7 (PDR_ON), X2.1 (TRI-STATE), X2.4 (VDD); also elsewhere on the board
VDDIO: R44.1, R45.1, R46.1, R47.1, R48.1, R49.1, R50.1, R51.1, R53.1; also elsewhere on the board

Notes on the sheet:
32.768Khz
40Mhz
PMIC
